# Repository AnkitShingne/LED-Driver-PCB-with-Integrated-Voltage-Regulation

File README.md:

# LED Driver PCB with Integrated Voltage Regulation

## Overview
This repository contains the files and documentation for a PCB design project created using Eagle PCB design software. The project focuses on designing an LED driver circuit with integrated voltage regulation.

## Files Included
* __'project.sch'__: Eagle schematic file containing the LED driver circuit design.
*  __'project.brd'__: Eagle board layout file with components placed and routed.
* __'gerber_files'__: Folder containing Gerber files for manufacturing the PCB.
* __'README.md'__: This readme file providing project information and instructions.

## Project Details
The LED driver PCB is designed to regulate voltage and ensure consistent LED illumination while managing input voltage fluctuations. The schematic and board layout files are included for reference and modification.

## Usage
1. Open __'project.sch'__ in Eagle to view the schematic design.
2. Open __'project.brd'__ in Eagle to view the board layout.
3. The __'gerber_files/'__ folder contains Gerber files required for manufacturing the PCB.

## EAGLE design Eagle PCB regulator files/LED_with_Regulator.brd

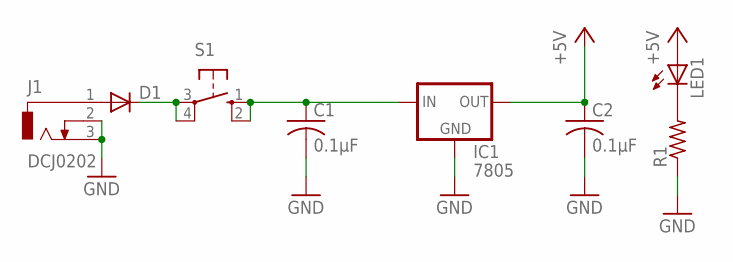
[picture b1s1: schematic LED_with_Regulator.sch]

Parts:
C1, C2: 0.1µF; C025-025X050
D1: DIODE-D-7.5; D-7.5
IC1: 7805; 78XXL
J1: DCJ0202
LED1: LED5MM
R1: R-US_0204/5; 0204/5
S1: 10-XX; B3F-10XX

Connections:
+5V: C2.1, IC1.OUT, LED1.A
GND: C1.2, C2.2, IC1.GND, J1.2, J1.3, R1.1
unnamed: D1.A, J1.1
unnamed: LED1.K (C), R1.2
unnamed: D1.C, S1.3, S1.4 (P1)
unnamed: C1.1, IC1.IN, S1.1 (S), S1.2 (S1)

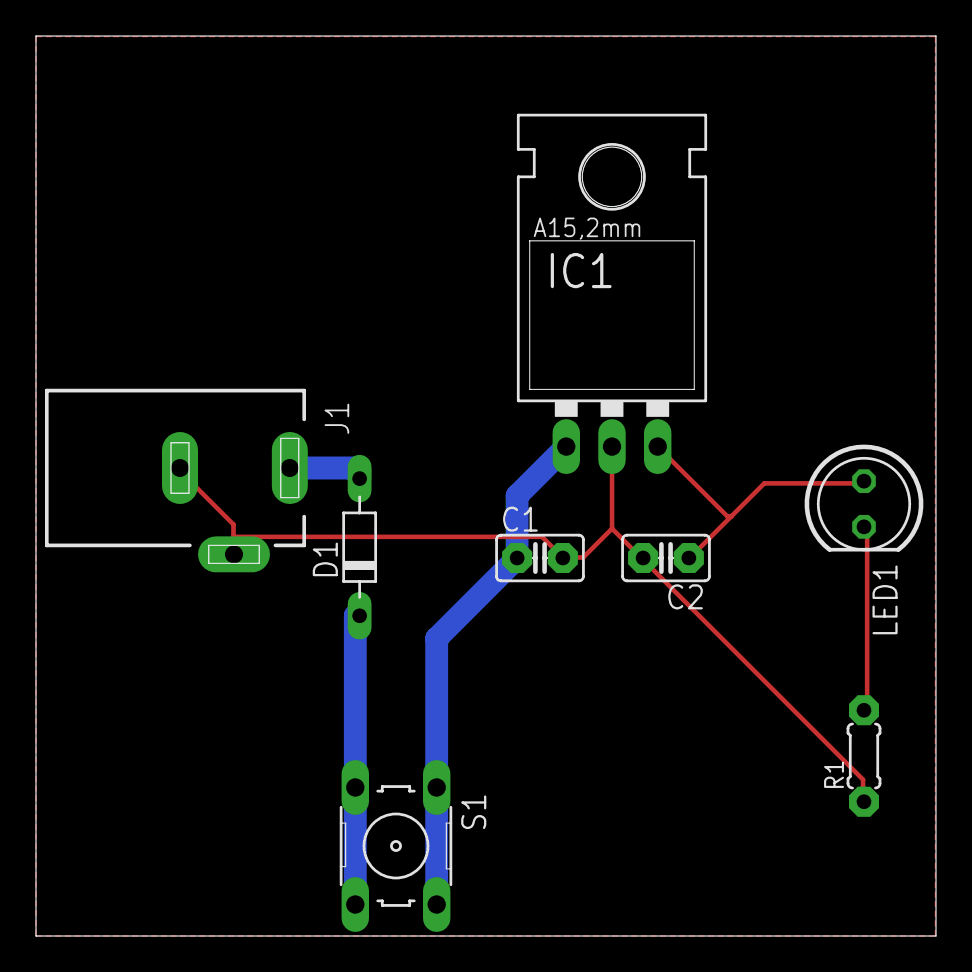
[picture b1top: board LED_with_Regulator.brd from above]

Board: 2 copper layers, 50.0 x 50.0 mm, 8 parts (0 on the bottom side), 6 nets.
